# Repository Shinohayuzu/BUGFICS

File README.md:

# BUGFICS
BUGFICS is hexapod robot. for my Labo.

RaspBerryPi zero + PCA9685

20 Servos.

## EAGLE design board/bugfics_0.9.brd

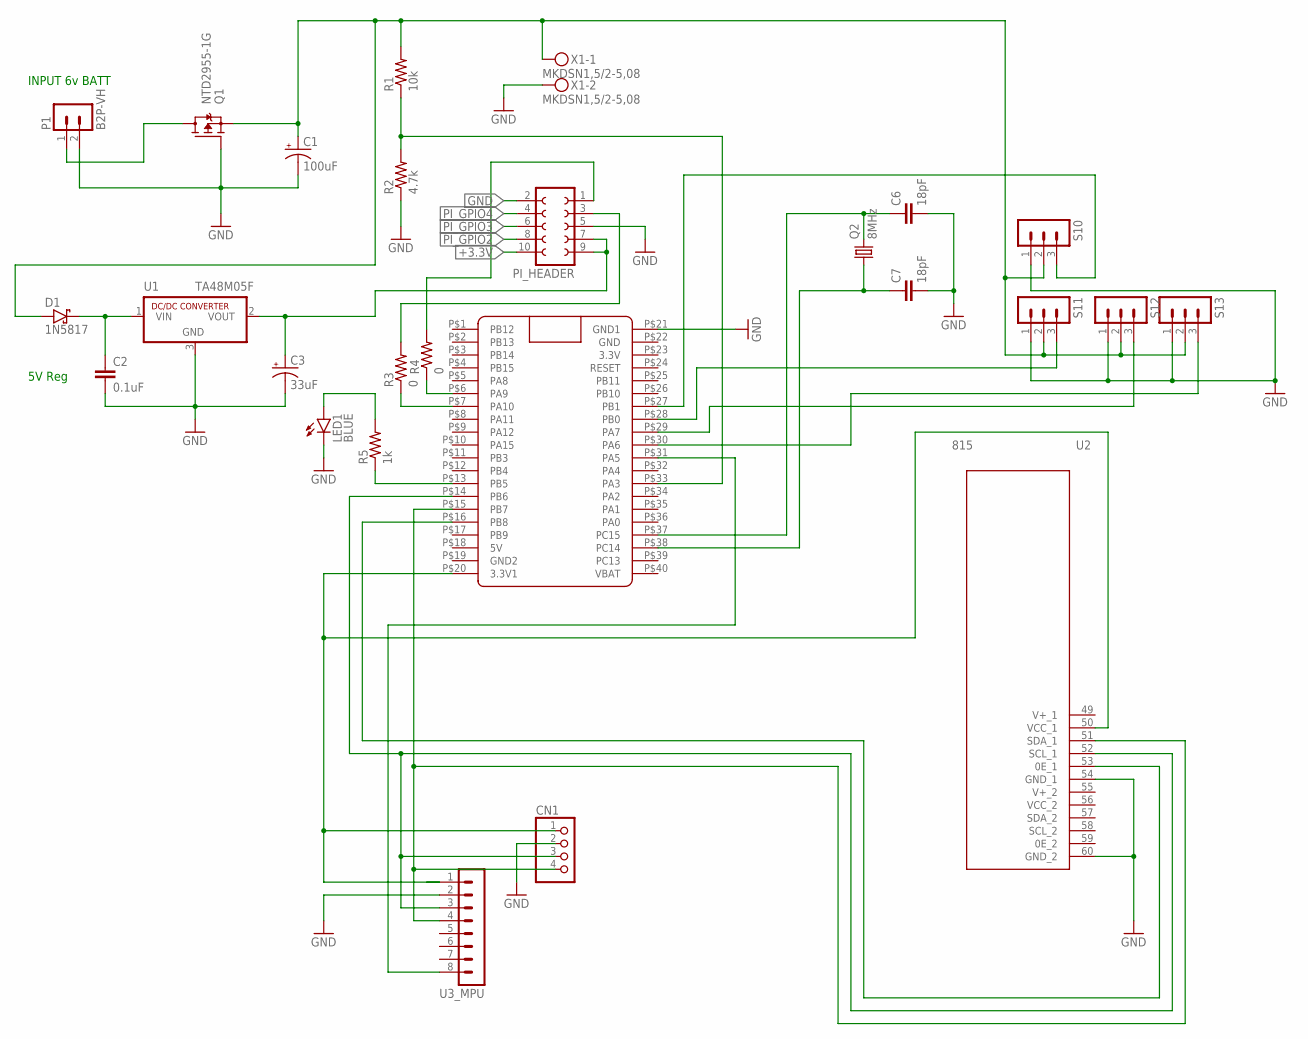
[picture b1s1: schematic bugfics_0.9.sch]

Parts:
C1: 100uF; E2-5
C2: 0.1uF; C025-025X050
C3: 33uF; E2-5
C6, C7: 18pF; C050-025X075
CN1: PINHD-1X4; 1X04
D1: 1N5817; DO41-3
LED1: BLUE; LED3MM
P1: B2P-VH
PI_HEADER: FE05-2W
Q1: NTD2955-1G; IPAK_CASE_369D
Q2: 8MHz; HC49/S
R1: 10k; 0207/7
R2: 4.7k; 0207/7
R3, R4: 0; 0207/7
R5: 1k; 0207/7
S10, S11, S12, S13: MA03-1
U1: TA48M05F; TO252
U2: 815
U3_MPU: MA08-1
U$1: BLUE_PILL
X1: MKDSN1,5/2-5,08

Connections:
+3.3V: PI_HEADER.10
GND: C1.-, C2.2, C3.-, C6.2, C7.2, CN1.2, LED1.K (C), P1.2, PI_HEADER.2, PI_HEADER.5, Q1.G, R2.1, S10.1, S11.1, S12.1, S13.1, U1.3 (GND), U2.54 (GND_1), U2.60 (GND_2), U3_MPU.2, U$1.P$21 (GND1), X1.2
unnamed: R3.1, U$1.P$7 (PA10)
unnamed: P1.1, Q1.D
unnamed: C1.+, D1.A, Q1.S, R1.2, S10.2, S11.2, S12.2, S13.2, X1.1
unnamed: R1.1, R2.2, U$1.P$33 (PA3)
unnamed: C2.1, D1.C, U1.1 (VIN)
unnamed: S13.3, U$1.P$30 (PA6)
unnamed: S12.3, U$1.P$29 (PA7)
unnamed: S11.3, U$1.P$28 (PB0)
unnamed: S10.3, U$1.P$27 (PB1)
unnamed: CN1.1, U2.50 (VCC_1), U3_MPU.1, U$1.P$20 (3.3V1)
unnamed: PI_HEADER.3, R3.2
unnamed: C3.+, PI_HEADER.7, PI_HEADER.9, U1.2 (VOUT)
unnamed: PI_HEADER.1, R4.2
unnamed: R4.1, U$1.P$6 (PA9)
unnamed: C6.1, Q2.2, U$1.P$37 (PC15)
unnamed: C7.1, Q2.1, U$1.P$38 (PC14)
unnamed: CN1.4, U2.51 (SDA_1), U3_MPU.4, U$1.P$15 (PB7)
unnamed: CN1.3, U2.52 (SCL_1), U3_MPU.3, U$1.P$14 (PB6)
unnamed: U2.53 (0E_1), U$1.P$16 (PB8)
unnamed: U3_MPU.8, U$1.P$31 (PA5)
unnamed: R5.1, U$1.P$13 (PB5)
unnamed: LED1.A, R5.2
PI_GPIO2: PI_HEADER.8
PI_GPIO3: PI_HEADER.6
PI_GPIO4: PI_HEADER.4

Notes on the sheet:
INPUT 6v BATT
5V Reg

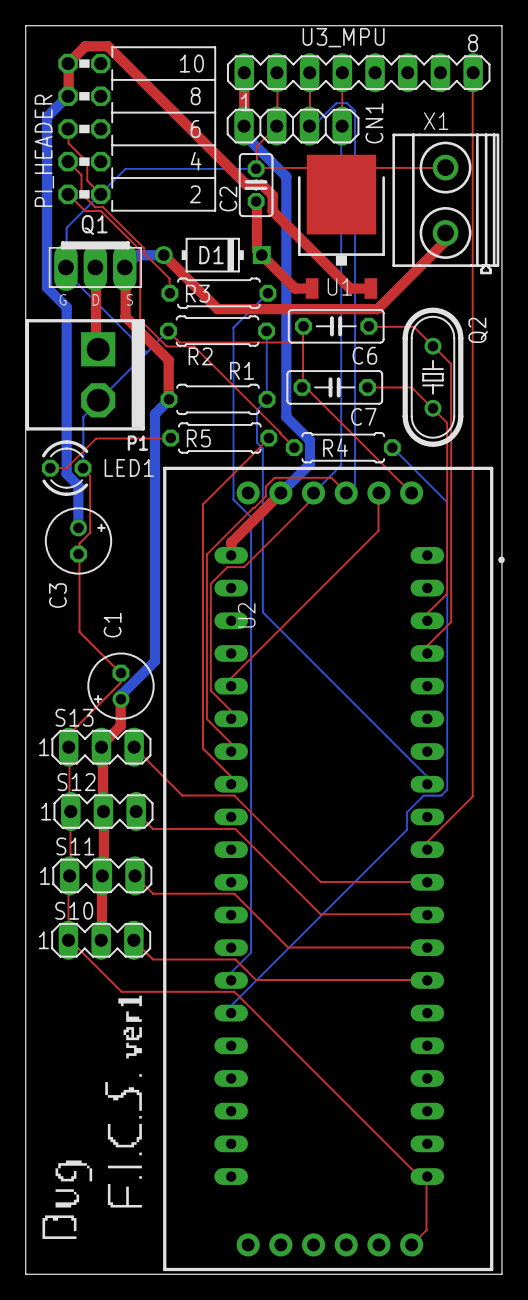
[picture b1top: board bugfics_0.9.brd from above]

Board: 2 copper layers, 37.0 x 97.0 mm, 26 parts (1 on the bottom side), 23 nets.

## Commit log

2022-06-19 PCBデータ追加

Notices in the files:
parts and their libraries:
con-jst-vh: Copyright (C) 2016, Bob Starr
